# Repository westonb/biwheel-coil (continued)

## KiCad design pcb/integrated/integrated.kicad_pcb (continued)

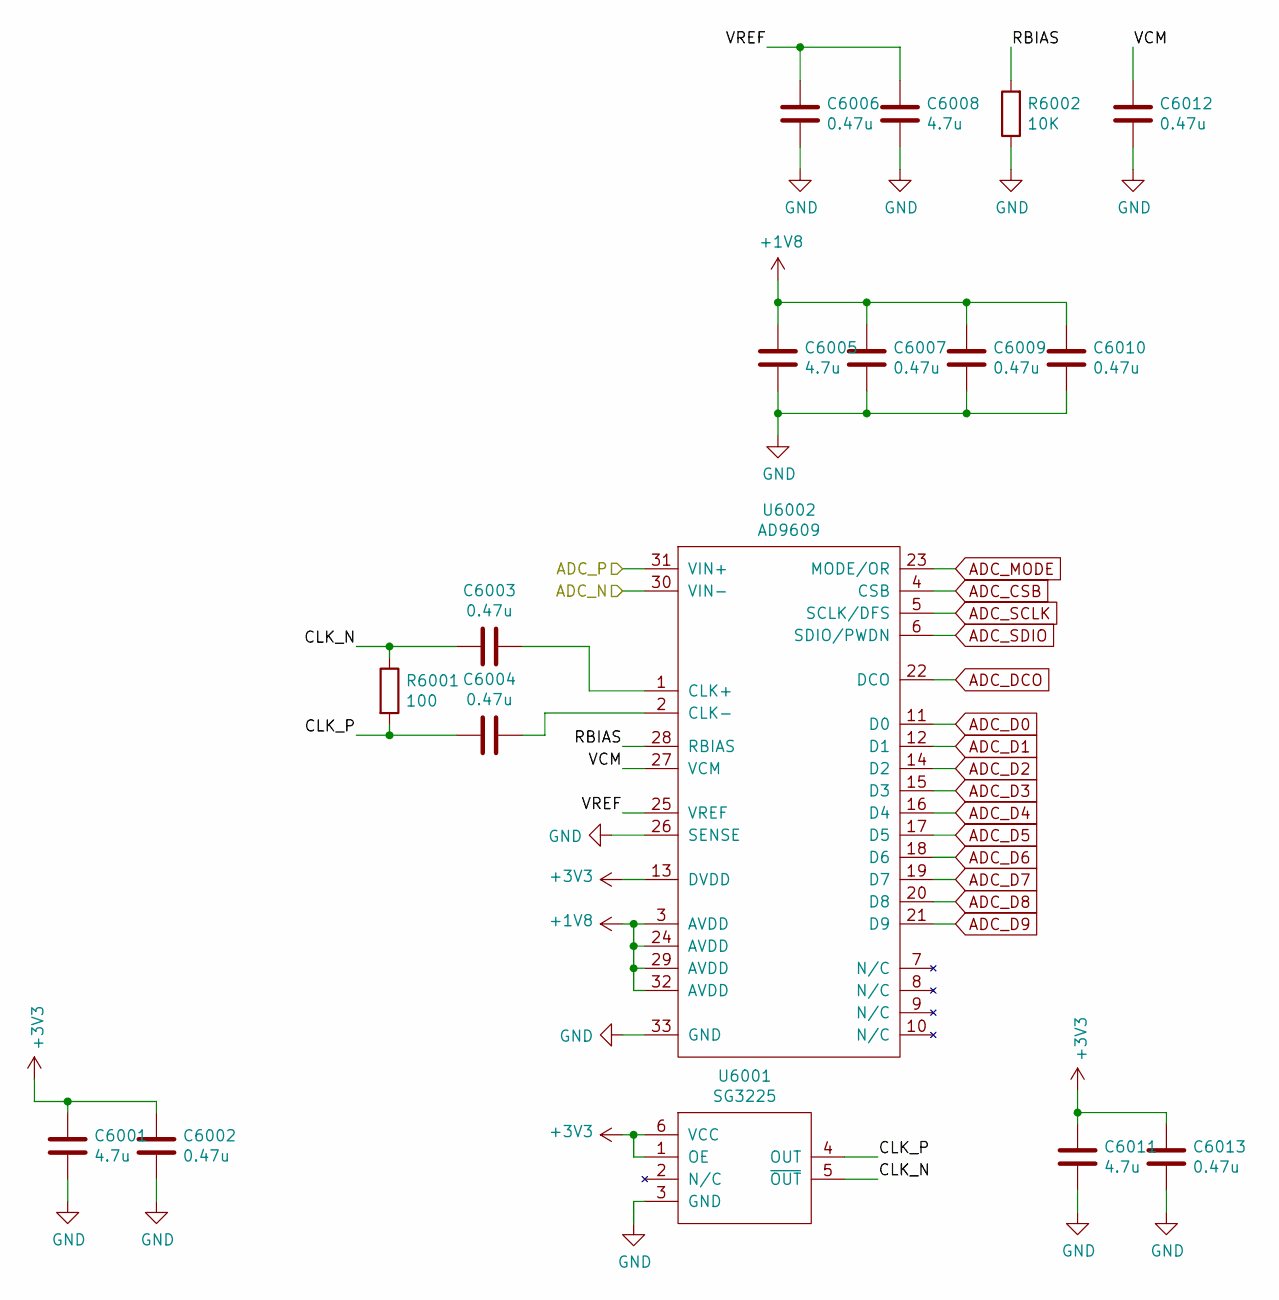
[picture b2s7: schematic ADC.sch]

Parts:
C6001, C6005, C6008, C6011: 4.7u; C_0402_1005Metric
C6002, C6003, C6004, C6006, C6007, C6009, C6010, C6012, C6013: 0.47u; C_0402_1005Metric
R6001: 100; R_0402_1005Metric
R6002: 10K; R_0402_1005Metric
U6001: SG3225
U6002: AD9609; QFN-32-1EP_5x5mm_P0.5mm_EP3.45x3.45mm

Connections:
+1V8: C6005.2, C6007.2, C6009.2, C6010.2, U6002.3 (AVDD), U6002.24 (AVDD), U6002.29 (AVDD), U6002.32 (AVDD); also elsewhere on the board
+3V3: C6001.2, C6002.2, C6011.2, C6013.2, U6001.1 (OE), U6001.6 (VCC), U6002.13 (DVDD); also elsewhere on the board
/Control/ADC/ADC_N: U6002.30 (VIN-); also elsewhere on the board
/Control/ADC/ADC_P: U6002.31 (VIN+); also elsewhere on the board
/Control/ADC/CLK_N: C6003.1, R6001.1, U6001.5 (~OUT)
/Control/ADC/CLK_P: C6004.1, R6001.2, U6001.4 (OUT)
/Control/ADC/RBIAS: R6002.2, U6002.28 (RBIAS)
/Control/ADC/VCM: C6012.2, U6002.27 (VCM)
/Control/ADC/VREF: C6006.2, C6008.2, U6002.25 (VREF)
ADC_CSB: U6002.4 (CSB); also elsewhere on the board
ADC_D0: U6002.11 (D0); also elsewhere on the board
ADC_D1: U6002.12 (D1); also elsewhere on the board
ADC_D2: U6002.14 (D2); also elsewhere on the board
ADC_D3: U6002.15 (D3); also elsewhere on the board
ADC_D4: U6002.16 (D4); also elsewhere on the board
ADC_D5: U6002.17 (D5); also elsewhere on the board
ADC_D6: U6002.18 (D6); also elsewhere on the board
ADC_D7: U6002.19 (D7); also elsewhere on the board
ADC_D8: U6002.20 (D8); also elsewhere on the board
ADC_D9: U6002.21 (D9); also elsewhere on the board
ADC_DCO: U6002.22 (DCO); also elsewhere on the board
ADC_MODE: U6002.23 (MODE/OR); also elsewhere on the board
ADC_SCLK: U6002.5 (SCLK/DFS); also elsewhere on the board
ADC_SDIO: U6002.6 (SDIO/PWDN); also elsewhere on the board
GND: C6001.1, C6002.1, C6005.1, C6006.1, C6007.1, C6008.1, C6009.1, C6010.1, C6011.1, C6012.1, C6013.1, R6002.1, U6001.3 (GND), U6002.26 (SENSE), U6002.33 (GND); also elsewhere on the board
unnamed: C6003.2, U6002.1 (CLK+)
unnamed: C6004.2, U6002.2 (CLK-)

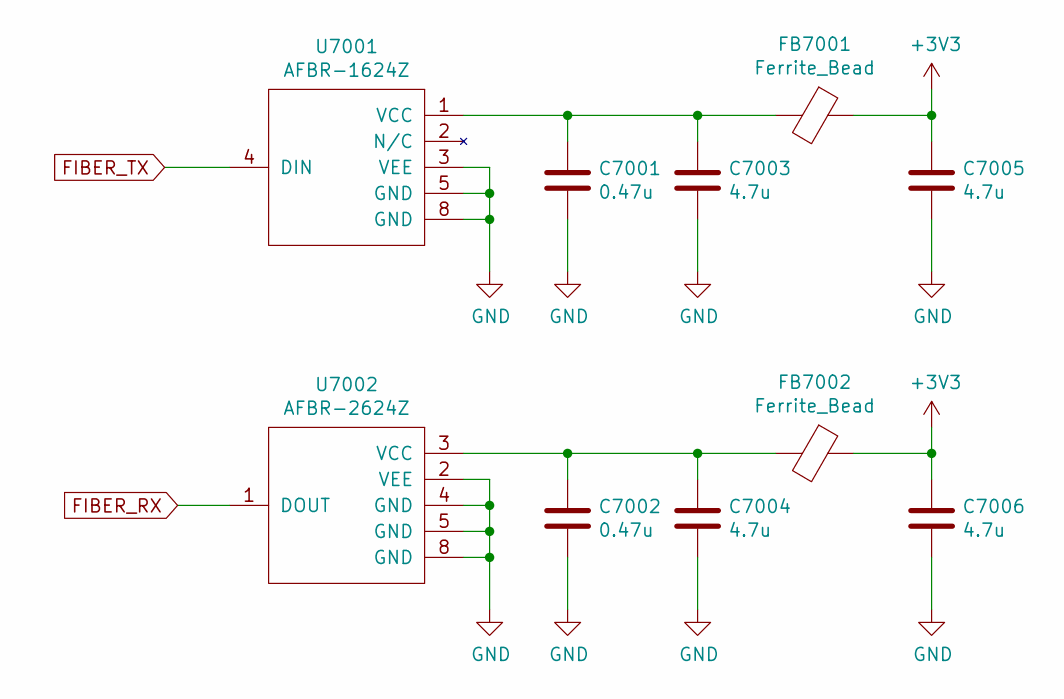
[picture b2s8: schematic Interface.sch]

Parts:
C7001, C7002: 0.47u; C_0402_1005Metric
C7003, C7004, C7005, C7006: 4.7u; C_0402_1005Metric
FB7001, FB7002: Ferrite_Bead; L_0402_1005Metric
U7001: AFBR-1624Z; versatile-link_horizontal
U7002: AFBR-2624Z; versatile-link_horizontal

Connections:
+3V3: C7005.1, C7006.1, FB7001.1, FB7002.1; also elsewhere on the board
FIBER_RX: U7002.1 (DOUT); also elsewhere on the board
FIBER_TX: U7001.4 (DIN); also elsewhere on the board
GND: C7001.2, C7002.2, C7003.2, C7004.2, C7005.2, C7006.2, U7001.3 (VEE), U7001.5 (GND), U7001.8 (GND), U7002.2 (VEE), U7002.4 (GND), U7002.5 (GND), U7002.8 (GND); also elsewhere on the board
unnamed: C7001.1, C7003.1, FB7001.2, U7001.1 (VCC)
unnamed: C7002.1, C7004.1, FB7002.2, U7002.3 (VCC)

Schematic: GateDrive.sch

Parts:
C11001, C11003, C11004: 0.47u; C_0603_1608Metric
C11002, C11005, C11006: 4.7u; C_0805_2012Metric
FB11001: Ferrite_Bead_Small; L_0805_2012Metric
L11001: CM_CHOKE; SRF2012
R11001, R11004: 4.7K; R_0603_1608Metric
R11002, R11003: 1; R_0805_2012Metric
U11001: UCC5350SB; SOIC-8_3.9x4.9mm_P1.27mm
U11002: R15P21503D; SIP7-5

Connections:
+3V3: C11001.1, U11001.1 (VCC1); also elsewhere on the board
+12V: L11001.3; also elsewhere on the board
/Inverter/Gate Drive 1/Gate: FB11001.1, R11004.2; also elsewhere on the board
/Inverter/Gate Drive 1/V-: C11004.1, C11006.2, U11001.8 (VEE2), U11002.5 (-VOUT)
GATE1: R11001.2, U11001.2 (IN+); also elsewhere on the board
GND: C11001.2, L11001.1, R11001.1, U11001.3 (IN-), U11001.4 (GND1); also elsewhere on the board
unnamed: C11002.1, L11001.4, U11002.1 (+VIN)
unnamed: C11002.2, L11001.2, U11002.2 (-VIN)
unnamed: FB11001.2, R11002.1, R11003.1
unnamed: R11002.2, U11001.6 (OUTH)
unnamed: R11003.2, U11001.7 (OUTL)

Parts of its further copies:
C12001, C12003, C12004, C13001, C13003, C13004, C14001, C14003, C14004: 0.47u; C_0603_1608Metric
C12002, C12005, C12006, C13002, C13005, C13006, C14002, C14005, C14006: 4.7u; C_0805_2012Metric
FB12001, FB13001, FB14001: Ferrite_Bead_Small; L_0805_2012Metric
L12001, L13001, L14001: CM_CHOKE; SRF2012
R12001, R12004, R13001, R13004, R14001, R14004: 4.7K; R_0603_1608Metric
R12002, R12003, R13002, R13003, R14002, R14003: 1; R_0805_2012Metric
U12001, U13001, U14001: UCC5350SB; SOIC-8_3.9x4.9mm_P1.27mm
U12002, U13002, U14002: R15P21503D; SIP7-5

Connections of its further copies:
+3V3: C12001.1, C13001.1, C14001.1, U12001.1 (VCC1), U13001.1 (VCC1), U14001.1 (VCC1); also elsewhere on the board
+12V: L12001.3, L13001.3, L14001.3; also elsewhere on the board
/Inverter/Gate Drive 2/Gate: FB12001.1, R12004.2; also elsewhere on the board
/Inverter/Gate Drive 2/V-: C12004.1, C12006.2, U12001.8 (VEE2), U12002.5 (-VOUT)
/Inverter/Gate Drive 3/Gate: FB13001.1, R13004.2; also elsewhere on the board
/Inverter/Gate Drive 3/Source: C13003.1, C13004.2, C13005.2, C13006.1, R13004.1, U13002.6 (COM); also elsewhere on the board
/Inverter/Gate Drive 3/V+: C13003.2, C13005.1, U13001.5 (VCC2), U13002.7 (+VOUT)
/Inverter/Gate Drive 3/V-: C13004.1, C13006.2, U13001.8 (VEE2), U13002.5 (-VOUT)
/Inverter/Gate Drive 4/Gate: FB14001.1, R14004.2; also elsewhere on the board
/Inverter/Gate Drive 4/Source: C14003.1, C14004.2, C14005.2, C14006.1, R14004.1, U14002.6 (COM); also elsewhere on the board
/Inverter/Gate Drive 4/V+: C14003.2, C14005.1, U14001.5 (VCC2), U14002.7 (+VOUT)
/Inverter/Gate Drive 4/V-: C14004.1, C14006.2, U14001.8 (VEE2), U14002.5 (-VOUT)
GATE2: R12001.2, U12001.2 (IN+); also elsewhere on the board
GATE3: R13001.2, U13001.2 (IN+); also elsewhere on the board
GATE4: R14001.2, U14001.2 (IN+); also elsewhere on the board
GND: C12001.2, C13001.2, C14001.2, L12001.1, L13001.1, L14001.1, R12001.1, R13001.1, R14001.1, U12001.3 (IN-), U12001.4 (GND1), U13001.3 (IN-), U13001.4 (GND1), U14001.3 (IN-), U14001.4 (GND1); also elsewhere on the board
unnamed: C12002.1, L12001.4, U12002.1 (+VIN)
unnamed: C12002.2, L12001.2, U12002.2 (-VIN)
unnamed: C13002.1, L13001.4, U13002.1 (+VIN)
unnamed: C13002.2, L13001.2, U13002.2 (-VIN)
unnamed: C14002.1, L14001.4, U14002.1 (+VIN)
unnamed: C14002.2, L14001.2, U14002.2 (-VIN)
unnamed: FB12001.2, R12002.1, R12003.1
unnamed: FB13001.2, R13002.1, R13003.1
unnamed: FB14001.2, R14002.1, R14003.1
unnamed: R12002.2, U12001.6 (OUTH)
unnamed: R12003.2, U12001.7 (OUTL)
unnamed: R13002.2, U13001.6 (OUTH)
unnamed: R13003.2, U13001.7 (OUTL)
unnamed: R14002.2, U14001.6 (OUTH)
unnamed: R14003.2, U14001.7 (OUTL)

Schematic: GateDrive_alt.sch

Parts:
C11001, C11003, C11004: 0.47u; C_0603_1608Metric
C11002, C11005, C11006: 4.7u; C_0805_2012Metric
FB11001, FB11002, FB11003: Ferrite_Bead_Small; L_0805_2012Metric
L11001: CM_CHOKE; SRF2012
R11001, R11004: 4.7K; R_0603_1608Metric
R11002, R11003, R11005, R11006: 1; R_0805_2012Metric
U11001: UCC5350SB; SOIC-8_3.9x4.9mm_P1.27mm
U11002: R15P21503D; SIP7-5

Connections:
+3V3: C11001.1, U11001.1 (VCC1); also elsewhere on the board
+12V: L11001.3; also elsewhere on the board
/Inverter/Gate Drive 1/Gate: FB11001.1, R11004.2; also elsewhere on the board
/Inverter/Gate Drive 1/V-: C11004.1, C11006.2, U11001.8 (VEE2), U11002.5 (-VOUT)
GATE1: R11001.2, U11001.2 (IN+); also elsewhere on the board
GND: C11001.2, L11001.1, R11001.1, U11001.3 (IN-), U11001.4 (GND1); also elsewhere on the board
unnamed: C11002.1, L11001.4, U11002.1 (+VIN)
unnamed: C11002.2, L11001.2, U11002.2 (-VIN)
unnamed: FB11001.2, R11002.1, R11003.1
unnamed: R11002.2, U11001.6 (OUTH)
unnamed: R11003.2, U11001.7 (OUTL)

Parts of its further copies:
C12001, C12003, C12004, C13001, C13003, C13004, C14001, C14003, C14004: 0.47u; C_0603_1608Metric
C12002, C12005, C12006, C13002, C13005, C13006, C14002, C14005, C14006: 4.7u; C_0805_2012Metric
FB12001, FB12002, FB12003, FB13001, FB13002, FB13003, FB14001, FB14002, FB14003: Ferrite_Bead_Small; L_0805_2012Metric
L12001, L13001, L14001: CM_CHOKE; SRF2012
R12001, R12004, R13001, R13004, R14001, R14004: 4.7K; R_0603_1608Metric
R12002, R12003, R12005, R12006, R13002, R13003, R13005, R13006, R14002, R14003, R14005, R14006: 1; R_0805_2012Metric
U12001, U13001, U14001: UCC5350SB; SOIC-8_3.9x4.9mm_P1.27mm
U12002, U13002, U14002: R15P21503D; SIP7-5

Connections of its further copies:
+3V3: C12001.1, C13001.1, C14001.1, U12001.1 (VCC1), U13001.1 (VCC1), U14001.1 (VCC1); also elsewhere on the board
+12V: L12001.3, L13001.3, L14001.3; also elsewhere on the board
/Inverter/Gate Drive 2/Gate: FB12001.1, R12004.2; also elsewhere on the board
/Inverter/Gate Drive 2/V-: C12004.1, C12006.2, U12001.8 (VEE2), U12002.5 (-VOUT)
/Inverter/Gate Drive 3/Gate: FB13001.1, R13004.2; also elsewhere on the board
/Inverter/Gate Drive 3/Source: C13003.1, C13004.2, C13005.2, C13006.1, R13004.1, U13002.6 (COM); also elsewhere on the board
/Inverter/Gate Drive 3/V+: C13003.2, C13005.1, U13001.5 (VCC2), U13002.7 (+VOUT)
/Inverter/Gate Drive 3/V-: C13004.1, C13006.2, U13001.8 (VEE2), U13002.5 (-VOUT)
/Inverter/Gate Drive 4/Gate: FB14001.1, R14004.2; also elsewhere on the board
/Inverter/Gate Drive 4/Source: C14003.1, C14004.2, C14005.2, C14006.1, R14004.1, U14002.6 (COM); also elsewhere on the board
/Inverter/Gate Drive 4/V+: C14003.2, C14005.1, U14001.5 (VCC2), U14002.7 (+VOUT)
/Inverter/Gate Drive 4/V-: C14004.1, C14006.2, U14001.8 (VEE2), U14002.5 (-VOUT)
DRIVE_AUX+: R12005.1; also elsewhere on the board
GATE2: R12001.2, U12001.2 (IN+); also elsewhere on the board
GATE3: R13001.2, U13001.2 (IN+); also elsewhere on the board
GATE4: R14001.2, U14001.2 (IN+); also elsewhere on the board
GND: C12001.2, C13001.2, C14001.2, L12001.1, L13001.1, L14001.1, R12001.1, R13001.1, R14001.1, U12001.3 (IN-), U12001.4 (GND1), U13001.3 (IN-), U13001.4 (GND1), U14001.3 (IN-), U14001.4 (GND1); also elsewhere on the board
unnamed: C12002.1, L12001.4, U12002.1 (+VIN)
unnamed: C12002.2, L12001.2, U12002.2 (-VIN)
unnamed: C13002.1, L13001.4, U13002.1 (+VIN)
unnamed: C13002.2, L13001.2, U13002.2 (-VIN)
unnamed: C14002.1, L14001.4, U14002.1 (+VIN)
unnamed: C14002.2, L14001.2, U14002.2 (-VIN)
unnamed: FB12001.2, R12002.1, R12003.1
unnamed: FB12002.1, R12005.2
unnamed: FB12003.1, R12006.2
unnamed: FB13001.2, R13002.1, R13003.1
unnamed: FB14001.2, R14002.1, R14003.1
unnamed: R12002.2, U12001.6 (OUTH)
unnamed: R12003.2, U12001.7 (OUTL)
unnamed: R13002.2, U13001.6 (OUTH)
unnamed: R13003.2, U13001.7 (OUTL)
unnamed: R14002.2, U14001.6 (OUTH)
unnamed: R14003.2, U14001.7 (OUTL)
PWRGND: R12006.1; also elsewhere on the board

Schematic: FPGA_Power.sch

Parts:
C4001: 100u; C_0805_2012Metric
C4002, C4003, C4004, C4023: 47u; C_0805_2012Metric
C4005, C4006, C4007, C4008, C4009, C4011, C4013, C4014: 4.7u; C_0402_1005Metric
C4010, C4012, C4015, C4016, C4017, C4018, C4019, C4022, C4024, C4025, C4026: 0.47u; C_0402_1005Metric
U3001: XC7S25-L1FTGB196; FTGB196

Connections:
+1V0: C4001.1, C4002.1, C4005.1, C4006.1, C4011.1, C4012.1, C4016.1, C4019.1, C4022.1, U3001.D6 (VCCINT), U3001.D8 (VCCINT), U3001.E5 (VCCBRAM), U3001.E7 (VCCINT), U3001.E9 (VCCINT), U3001.F6 (VCCINT), U3001.G5 (VCCBRAM), U3001.G9 (VCCINT), U3001.H6 (VCCINT), U3001.J5 (VCCBRAM), U3001.J9 (VCCINT), U3001.K6 (VCCINT), U3001.K8 (VCCINT); also elsewhere on the board
+1V8: C4003.1, C4007.1, C4010.1, C4015.1, C4026.1, U3001.F10 (VCCAUX), U3001.H10 (VCCAUX), U3001.K10 (VCCAUX), U3001.L9 (VCCAUX); also elsewhere on the board
+3V3: C4004.1, C4008.1, C4009.1, C4013.1, C4014.1, C4017.1, C4018.1, C4023.1, C4024.1, C4025.1, U3001.G2 (VCCO_34), U3001.G13 (VCCO_14), U3001.K2 (VCCO_34), U3001.K13 (VCCO_14), U3001.N2 (VCCO_34), U3001.N6 (VCCO_0), U3001.N8 (VCCO_0), U3001.N13 (VCCO_14); also elsewhere on the board
GND: C4001.2, C4002.2, C4003.2, C4004.2, C4005.2, C4006.2, C4007.2, C4008.2, C4009.2, C4010.2, C4011.2, C4012.2, C4013.2, C4014.2, C4015.2, C4016.2, C4017.2, C4018.2, C4019.2, C4022.2, C4023.2, C4024.2, C4025.2, C4026.2, U3001.A1 (GND), U3001.A6 (GND), U3001.A9 (GND), U3001.A11 (GND), U3001.A14 (GND), U3001.B4 (GND), U3001.B7 (GND), U3001.B9 (GND), U3001.C2 (GND), U3001.C6 (GND), U3001.C7 (GND), U3001.C8 (GND), U3001.C9 (GND), U3001.C13 (GND), U3001.D5 (GND), U3001.D7 (GND), U3001.D9 (GND), U3001.D11 (GND), U3001.E1 (GND), U3001.E3 (GND), U3001.E6 (GND), U3001.E8 (GND), U3001.E10 (GND), U3001.E14 (GND), U3001.F5 (GND), U3001.F9 (GND), U3001.G3 (GND), U3001.G6 (GND), U3001.G10 (GND), U3001.G12 (GND), U3001.H5 (GND), U3001.H9 (GND), U3001.J6 (GND), U3001.J10 (GND), U3001.K1 (GND), U3001.K5 (GND), U3001.K7 (GND), U3001.K9 (GND), U3001.K14 (GND), U3001.L4 (GND), U3001.L6 (GND), U3001.L8 (GND), U3001.L10 (GND), U3001.L11 (GND), U3001.N3 (GND), U3001.N5 (GND), U3001.N9 (GND), U3001.N12 (GND), U3001.P1 (GND), U3001.P14 (GND); also elsewhere on the board

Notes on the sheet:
Decoupling Capacitors Recomendation from UG483, Table 2-1
VCCINT
VCCBRAM
VCCAUX
VCCO14
Bank 0: 3V3 (config) Bank 14: 3V3 (due to config) Bank 34: 3V3 (LVDS) VCCINT: 1V0 VCCBRAM: 1V0 VCCAUX: 1V8
VCCO34
VCCO0

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
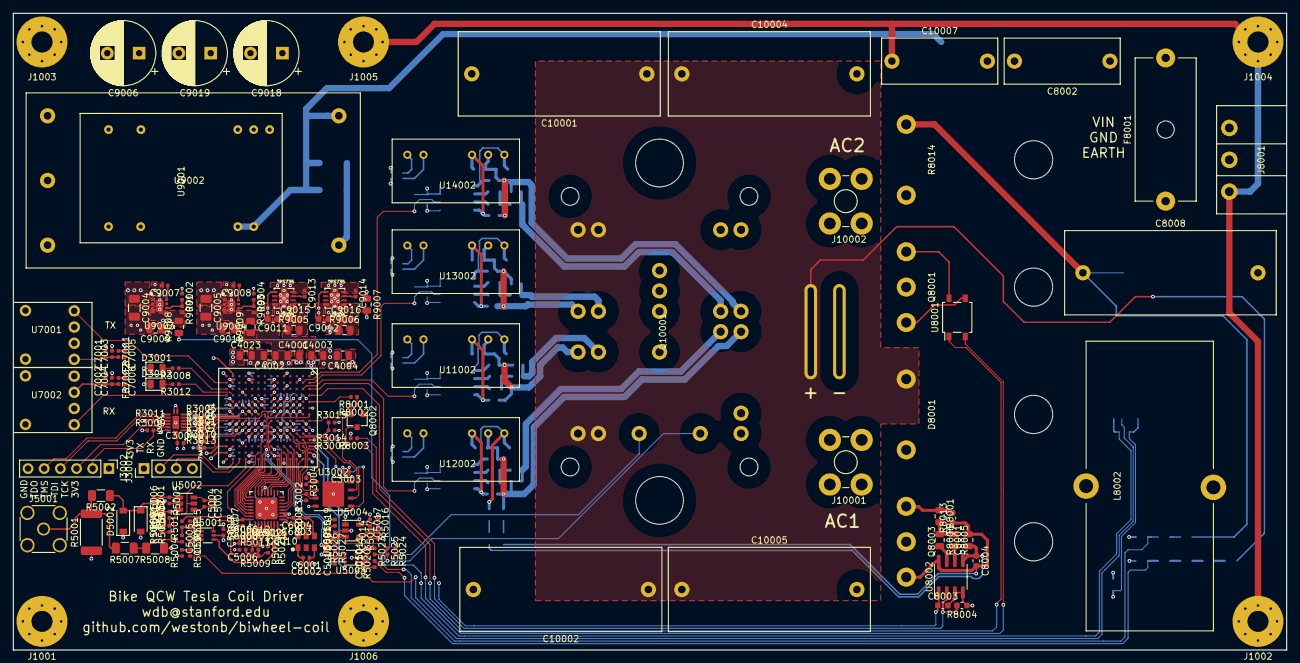
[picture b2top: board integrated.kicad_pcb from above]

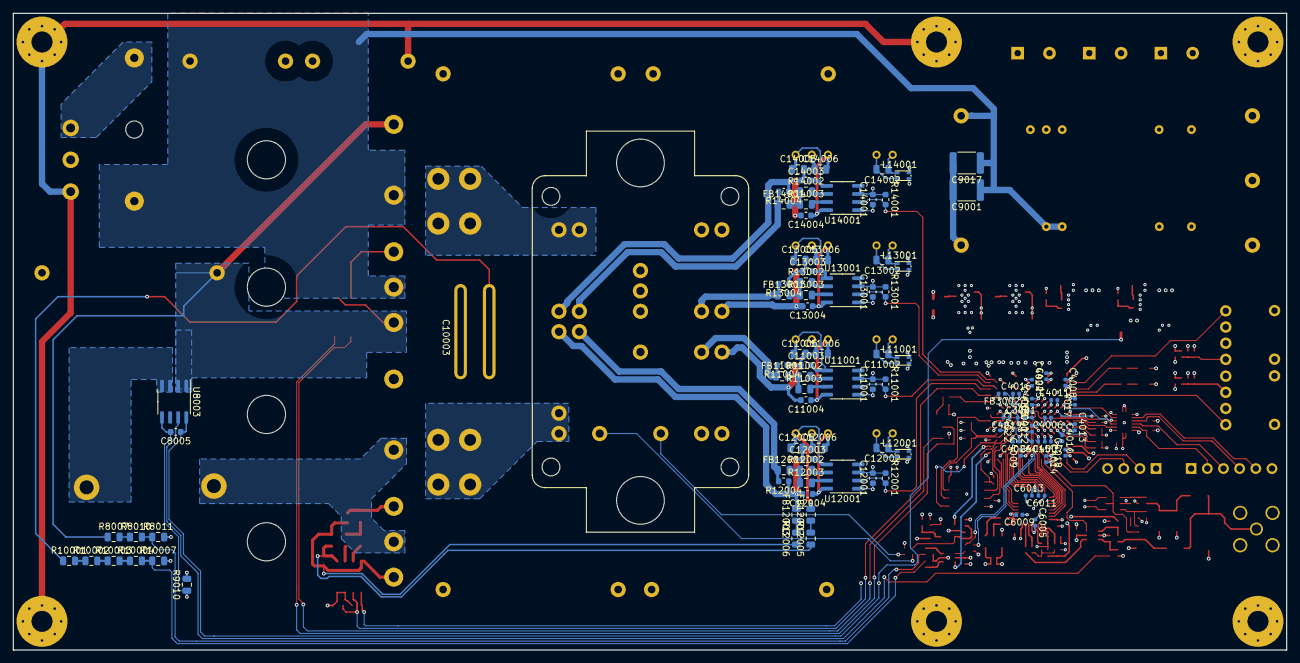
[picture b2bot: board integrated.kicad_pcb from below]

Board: 4 copper layers, 200.0 x 100.0 mm, 268 parts (96 on the bottom side), 167 nets.

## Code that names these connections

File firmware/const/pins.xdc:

set_property CFGBVS VCCO [current_design]
set_property CONFIG_VOLTAGE 3.3 [current_design]
set_property BITSTREAM.GENERAL.JTAG_XADC Disable [current_design]

#ADC data bus
set_property PACKAGE_PIN D13 [get_ports ADC_DATA[0]]
set_property IOSTANDARD LVCMOS33 [get_ports ADC_DATA[0]]
set_property PACKAGE_PIN D14 [get_ports ADC_DATA[1]]
set_property IOSTANDARD LVCMOS33 [get_ports ADC_DATA[1]]
set_property PACKAGE_PIN E12 [get_ports ADC_DATA[2]]
set_property IOSTANDARD LVCMOS33 [get_ports ADC_DATA[2]]
set_property PACKAGE_PIN E13 [get_ports ADC_DATA[3]]
set_property IOSTANDARD LVCMOS33 [get_ports ADC_DATA[3]]
set_property PACKAGE_PIN F12 [get_ports ADC_DATA[4]]
set_property IOSTANDARD LVCMOS33 [get_ports ADC_DATA[4]]
set_property PACKAGE_PIN F13 [get_ports ADC_DATA[5]]
set_property IOSTANDARD LVCMOS33 [get_ports ADC_DATA[5]]
set_property PACKAGE_PIN F14 [get_ports ADC_DATA[6]]
set_property IOSTANDARD LVCMOS33 [get_ports ADC_DATA[6]]
set_property PACKAGE_PIN G14 [get_ports ADC_DATA[7]]
set_property IOSTANDARD LVCMOS33 [get_ports ADC_DATA[7]]
set_property PACKAGE_PIN H14 [get_ports ADC_DATA[8]]
set_property IOSTANDARD LVCMOS33 [get_ports ADC_DATA[8]]
set_property PACKAGE_PIN H13 [get_ports ADC_DATA[9]]
set_property IOSTANDARD LVCMOS33 [get_ports ADC_DATA[9]]

#ADC other signals
set_property PACKAGE_PIN H11 [get_ports ADC_DCO]
set_property IOSTANDARD LVCMOS33 [get_ports ADC_DCO]
set_property PACKAGE_PIN J14 [get_ports ADC_MODE]
set_property IOSTANDARD LVCMOS33 [get_ports ADC_MODE]
set_property PACKAGE_PIN C14 [get_ports ADC_SCLK]
set_property IOSTANDARD LVCMOS33 [get_ports ADC_SCLK]
set_property PACKAGE_PIN D12 [get_ports ADC_SDIO]
set_property IOSTANDARD LVCMOS33 [get_ports ADC_SDIO]
set_property PACKAGE_PIN B14 [get_ports ADC_CS]
set_property IOSTANDARD LVCMOS33 [get_ports ADC_CS]

#ADC_MUX
set_property PACKAGE_PIN J13 [get_ports ADC_MUX]
set_property IOSTANDARD LVCMOS33 [get_ports ADC_MUX]

#XADC input pins
set_property PACKAGE_PIN G8 [get_ports VP_0]
set_property PACKAGE_PIN H7 [get_ports VN_0]

#XADC mux 
set_property PACKAGE_PIN A13 [get_ports XADC_MUX]
set_property IOSTANDARD LVCMOS33 [get_ports XADC_MUX]

#debug / status 
set_property PACKAGE_PIN P3 [get_ports LED1]
set_property IOSTANDARD LVCMOS33 [get_ports LED1]
set_property PACKAGE_PIN N4 [get_ports LED2]
set_property IOSTANDARD LVCMOS33 [get_ports LED2]
set_property PACKAGE_PIN N14 [get_ports DEBUG_TX]
set_property IOSTANDARD LVCMOS33 [get_ports DEBUG_TX]
set_property PACKAGE_PIN M14 [get_ports DEBUG_RX]
set_property IOSTANDARD LVCMOS33 [get_ports DEBUG_RX]

#interface
set_property PACKAGE_PIN P2 [get_ports FIBER_TX]
set_property IOSTANDARD LVCMOS33 [get_ports FIBER_TX]
set_property PACKAGE_PIN P4 [get_ports FIBER_RX]
set_property IOSTANDARD LVCMOS33 [get_ports FIBER_RX]

#comparators 
set_property PACKAGE_PIN L14 [get_ports ZCS]
set_property IOSTANDARD LVCMOS33 [get_ports ZCS]
set_property PACKAGE_PIN A12 [get_ports OVER_TEMP]
set_property IOSTANDARD LVCMOS33 [get_ports OVER_TEMP]


# bridge gate drive
set_property PACKAGE_PIN B3 [get_ports GATE1]
set_property IOSTANDARD LVCMOS33 [get_ports GATE1]
set_property PACKAGE_PIN A3 [get_ports GATE2]
set_property IOSTANDARD LVCMOS33 [get_ports GATE2]
set_property PACKAGE_PIN A2 [get_ports GATE3]
set_property IOSTANDARD LVCMOS33 [get_ports GATE3]
set_property PACKAGE_PIN B2 [get_ports GATE4]
set_property IOSTANDARD LVCMOS33 [get_ports GATE4]

#aux gate drive
set_property PACKAGE_PIN A5 [get_ports GATE_CHARGE]
set_property IOSTANDARD LVCMOS33 [get_ports GATE_CHARGE]
set_property PACKAGE_PIN A4 [get_ports GATE_BOOST]
set_property IOSTANDARD LVCMOS33 [get_ports GATE_BOOST]

#enable pullup on debug RX
set_property PULLUP TRUE [get_ports DEBUG_RX]

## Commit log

2019-09-09 moved project to git
2019-09-14 schematic fixes and component placement
2019-10-28 revised power input schematic
2019-10-30 routing, all componens placed on PCB
2019-11-03 routing progress
2019-11-04 redid power planes
2019-11-05 PCB routing finihsed, ready for design review
2019-11-07 finished design review and sent PCB to fab
2019-11-16 updated component values for schematic
2019-11-24 moved verilog files from old project and updated pins XDC file
2020-03-24 proof of concept controllers for QCW and boost converter
2020-04-26 started rewriting interfaces for picorv32
2020-04-27 more module intigration
2020-04-29 began module integration
2020-04-30 full system simulates and builds
2020-04-30 debugged boost converter
2020-05-02 first sparks
2020-05-09 modified makefile to use picolibc and started on command parser
2020-05-09 changed core and makefike to RV32IM to support multiply and divide
2020-05-16 added tesla coil modeling files
2020-05-17 added boost converter failsafes
2020-08-20 added endcaps and STEP file of PCB
2020-09-07 added MMC PCB
2020-11-15 CAD files and modeling
